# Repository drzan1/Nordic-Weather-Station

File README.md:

# Nordic-Weather-Station
Development of a weather monitoring system based on a Nordic microcontroller and multiple sensors. The system collects measurements such as temperature, humidity, air pressure, wind speed and water-related data, which are processed by the microcontroller. All the information will be displayed via Bluetooth or WIFI on the phone app, which i will develop myself. The project also includes the development of algorithms for analysing the collected data and predicting weather conditions. The project is currently in development.

THE PROJECT IS STILL IN THE PROCESS

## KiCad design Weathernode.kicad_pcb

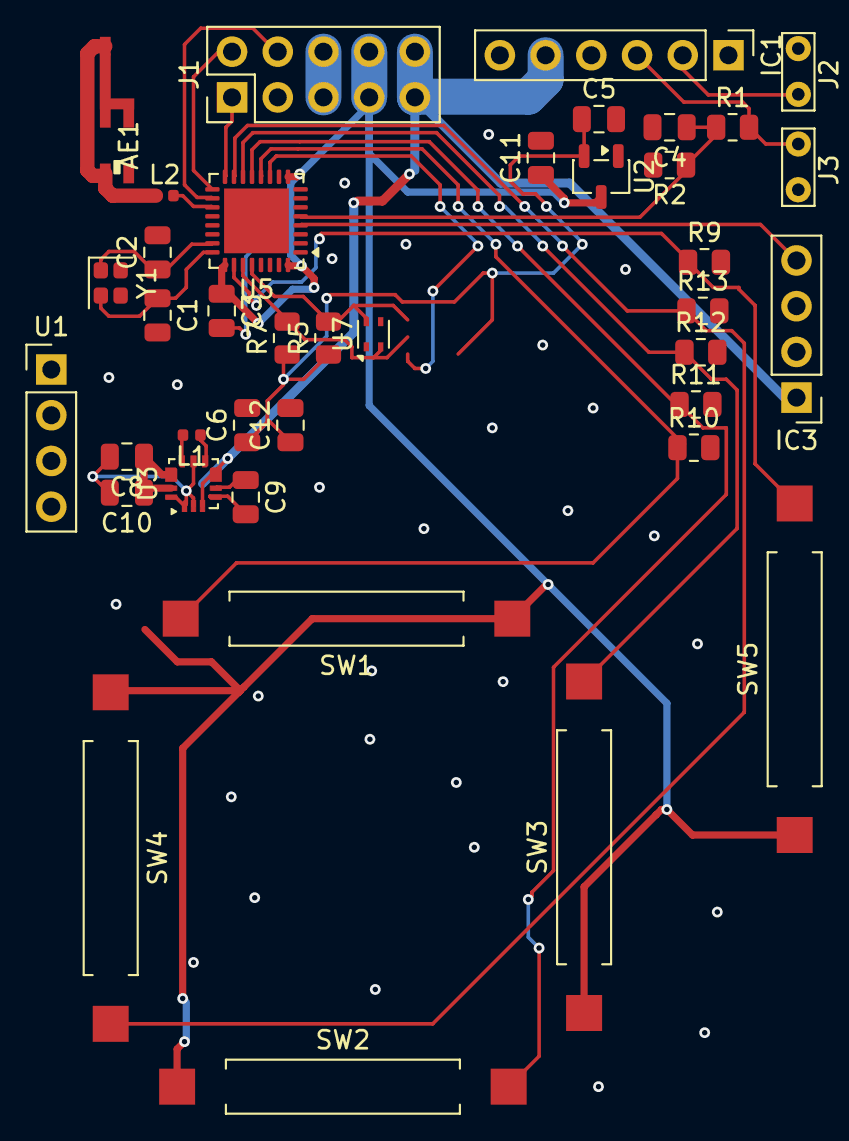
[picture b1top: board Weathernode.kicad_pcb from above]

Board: 2 copper layers, 39 parts (0 on the bottom side), 25 nets.

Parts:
AE1: Antenna; chip_2450AT18D0100_edge
C1, C2: 2p2; C_0805_2012Metric
C3, C4, C5, C6: 100n; C_0805_2012Metric
C8: 10u; C_0805_2012Metric
C9, C11, C12: 1u; C_0805_2012Metric
C10: 2u2; C_0805_2012Metric
IC1: TP4056; PinHeader_1x06_P2.54mm_Vertical
IC3: SAMIROB; PinHeader_1x04_P2.54mm_Vertical
J1: JLINK_V2; PinHeader_2x05_P2.54mm_Vertical
J2: Solar Cell; TestPoint_Bridge_Pitch2.54mm_Drill0.7mm
J3: Battery Cell; TestPoint_Bridge_Pitch2.54mm_Drill0.7mm
L1: 1u; L_0402_1005Metric
L2: 3n9; L_0402_1005Metric
R1, R2: 250k; R_0805_2012Metric
R5, R7: 4k7; R_0805_2012Metric
R9, R10, R11, R12, R13: 10k; R_0805_2012Metric
SW1, SW2, SW3, SW4, SW5: SW_Reed; SW_SPST_REED_CT10-XXXX-G2
U1: DHT30; PinHeader_1x04_P2.54mm_Vertical
U2: XC6206P182MR-G; SOT-23-3
U3: MAX77827AEFD; Maxim_FC2QFN-14_2.5x2.5mm_P0.5mm
U5: nRF52810-QCxx; QFN-32-1EP_5x5mm_P0.5mm_EP3.6x3.6mm
U7: SPL07-003; Sensirion_DFN-4_1.5x1.5mm_P0.8mm_SHT4x_NoCentralPad
Y1: 32M; Crystal_SMD_2016-4Pin_2.0x1.6mm

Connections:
+1V8: C12.1, U2.2 (VO)
+3.3V: C3.1, C5.1, C6.1, C8.1, C10.1, C11.1, J1.7 (Pin_5), J1.8 (Pin_6), R5.1, R7.1, SW1.2, SW2.2, SW3.2, SW4.2, SW5.2, U1.1 (VDD), U2.3 (VI), U3.11 (OUT), U3.13 (OUTS), U5.9 (VDD), U5.25 (VDD), U5.32 (VDD)
+5V: IC1.5 (OUT+), IC3.1 (VCC), J1.9 (Pin_7), J1.10 (Pin_8), U3.3 (EN), U3.6 (IN)
BAT_ADC: C4.1, R1.1, R2.1, U5.5 (P0.05/AIN3)
E: R12.1, SW3.1, U5.14 (P0.18)
GND: C1.2, C2.2, C3.2, C4.2, C5.2, C6.2, C8.2, C9.2, C10.2, C11.2, C12.2, IC1.1 (S-), IC1.4 (BAT-), IC1.6 (OUT-), IC3.2 (GND), J1.5 (Pin_9), J1.6 (Pin_10), R2.2, R9.2, R10.2, R11.2, R12.2, R13.2, U1.3 (GND), U2.1 (GND), U3.1 (SEL), U3.2 (POK), U3.4 (PGND), U3.9 (PGND), U3.14 (FPWM), U5.20 (VSS), U5.29 (VSS), U5.33 (VSS)
N: R10.1, SW1.1, U5.12 (P0.15)
unnamed: AE1.1 (A), L2.1
unnamed: IC1.3 (BAT+), J3.1, R1.2
unnamed: IC1.2 (S+), J2.1
unnamed: C9.1, U3.5 (BIAS)
unnamed: L1.1, U3.8 (LX1)
unnamed: L1.2, U3.10 (LX2)
unnamed: L2.2, U5.19 (ANT)
OSC_IN: C2.1, U5.23 (XC1), Y1.1
OSC_OUT: C1.1, U5.24 (XC2), Y1.2
RAIN: IC3.4 (AO), U5.4 (P0.04/AIN2)
S: R11.1, SW2.1, U5.13 (P0.16)
SCL: R5.2, U1.2 (SDA), U5.28 (P0.30/AIN6), U7.4 (SDA)
SDA: R7.2, U1.4 (SCL), U5.27 (P0.28/AIN4), U7.2 (SCL)
SWCLK: J1.2, U5.17 (SWDCLK)
SWDIO: J1.4, U5.18 (SWDIO)
W: R13.1, SW4.1, U5.15 (P0.20)
WSPEED: R9.1, SW5.1, U5.26 (P0.25)
nRST: J1.1, U5.16 (P0.21/~RESET)
